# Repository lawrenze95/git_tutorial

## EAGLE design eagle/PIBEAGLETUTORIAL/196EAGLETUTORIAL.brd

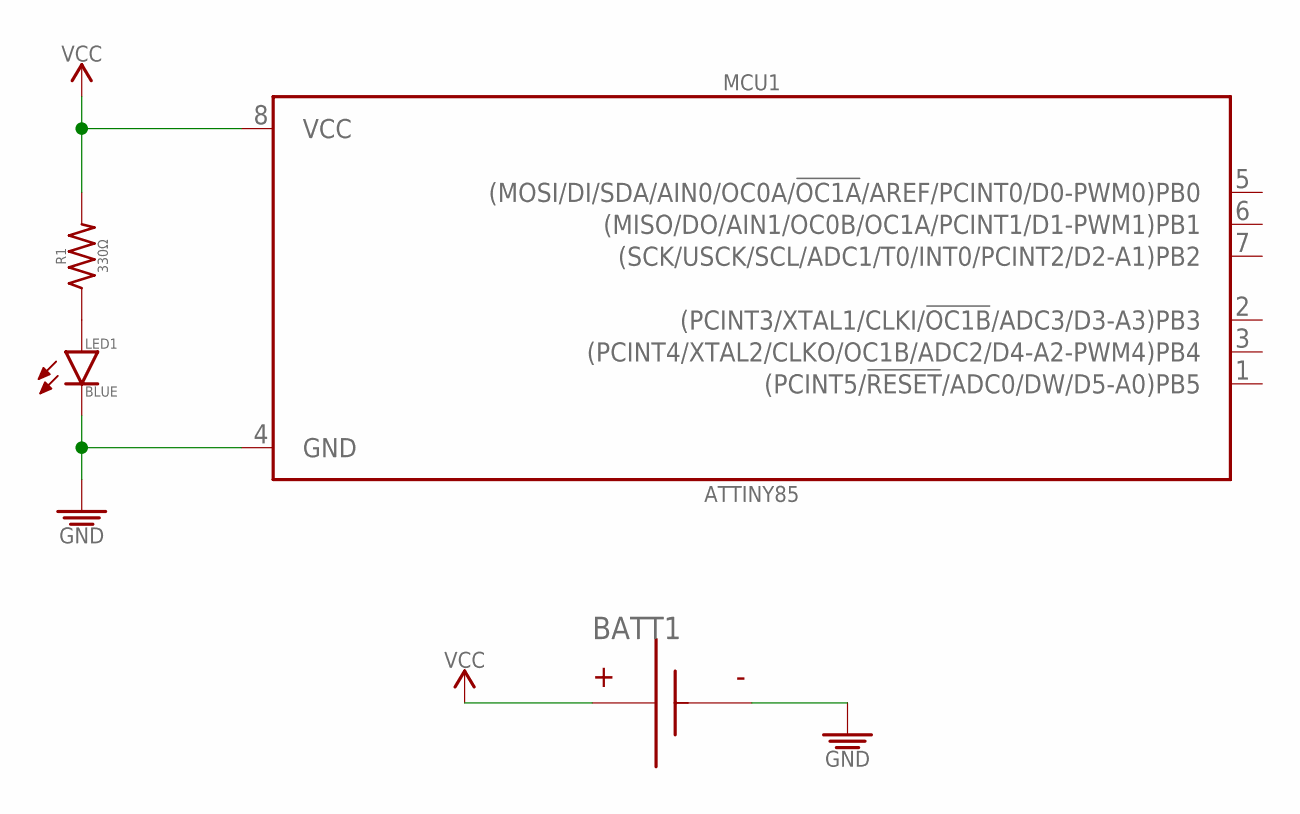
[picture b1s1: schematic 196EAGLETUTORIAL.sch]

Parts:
BATT1: BATTERYPTH_HOLES; DUAL_PTH_PADS
LED1: BLUE; LED_SMD-805_
MCU1: ATTINY85; DIP-8
R1: 330Ω; RESISTOR-PTH-0207/7

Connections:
GND: BATT1.- (N), LED1.K, MCU1.4 (GND)
unnamed: LED1.A, R1.1
VCC: MCU1.8 (VCC), R1.2

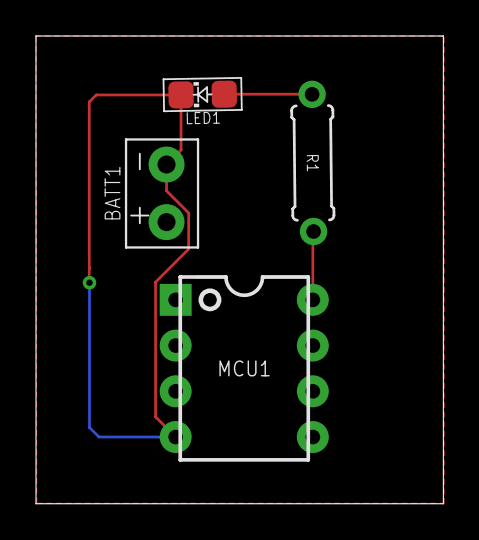
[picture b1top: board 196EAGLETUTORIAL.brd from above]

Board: 2 copper layers, 22.6 x 26.0 mm, 4 parts (0 on the bottom side), 3 nets.

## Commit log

2018-04-17 initialized
2018-04-17 change hello
2018-04-17 reset repo
